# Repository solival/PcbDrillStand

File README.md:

# PCB Drill Press Stand
This is small neat drill press stand designed to use laser printer engines widely sold on ebay/aliexpress.
This project based on http://www.thingiverse.com/thing:144333 by Mark Benson design with next improvements:

- Designed for engine body sized L=35-60mm D=30mm
- Shifted base hole to center drill according new motor diameter
- Added 3x 3mm super light LED holders focused on drill working area
- Added PCB with voltage regulator and connector for standard notebook power unit (which is used for drill and light). This can be easily changed on any power source up to 24v (only connector should be changed in this case)
- Added holes in slider to mount PCB
- Added hole on left side of fixed sliding wedge for balancing spring/rubber.

Apart from that no big changes. I print gears with 40% filament and all other parts with 20% filament. Works fine.

This thing on thingiverse: http://www.thingiverse.com/thing:766712

# Photos
Drill Press Stand assembled

---

Drilling area light

---

Assembled render front

---

Assembled render back:

---

LED Light Schematics

---

LED Light board layout

# Bill of Materials
## Mechanics
- ABS or PLA filament
- Drill chuck
- Threaded rod M5 (about 110mm)
- Threaded rod M8 (about 95mm and 80mm). One is for stand, second is for gear and fixed slider.
- 6x M8 nut, nyloc (better 8x for stand tightening)
- 4x 8mm washer
- 9x M3 18mm bolts
- 10x M3 nuts
- 6x 3mm washers
- 6x 3x12mm screws

## Electronics
- Motor from printer with body diameter 30mm and length between 35-60mm
- Female-Female du-pont wires 10cm (6x)
- 3x LED 3mm White
- 2.54mm 2-wire connector
- Jack plug (diameters must match your notebook power unit connector)
- Notebook power unit
- 2x3 pin header male
- LM7805 (or LM7812) voltage regulator
- 0.1uF and 0.33uF capacitors
- 3x 100 Ohm resistors (or 390 Ohm if LM7812 used)
- Prototype Board or etched PCB

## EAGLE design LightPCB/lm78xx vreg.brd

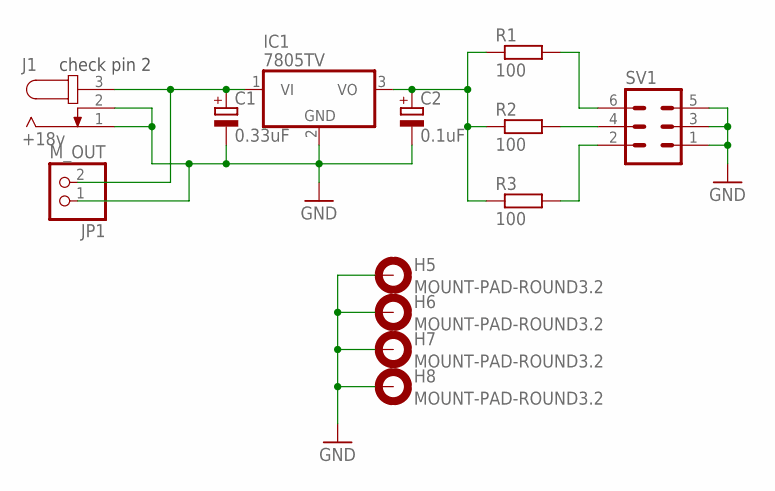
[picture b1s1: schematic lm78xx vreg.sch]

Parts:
C1: 0.33uF; E2,5-7
C2: 0.1uF; E2,5-7
H5, H6, H7, H8: MOUNT-PAD-ROUND3.2; 3,2-PAD
IC1: 7805TV; TO220V
J1: +18v; SPC4078
JP1: M_OUT; 1X02
R1, R2, R3: 100; R0805W
SV1: MA03-2

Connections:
GND: C1.-, C2.-, H5.B3,2, H6.B3,2, H7.B3,2, H8.B3,2, IC1.2 (GND), J1.1, J1.2, JP1.1, SV1.1, SV1.3, SV1.5
unnamed: C1.+, IC1.1 (VI), J1.3, JP1.2
unnamed: C2.+, IC1.3 (VO), R1.1, R2.1, R3.1
unnamed: R2.2, SV1.4
unnamed: R1.2, SV1.6
unnamed: R3.2, SV1.2

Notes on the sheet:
check pin 2

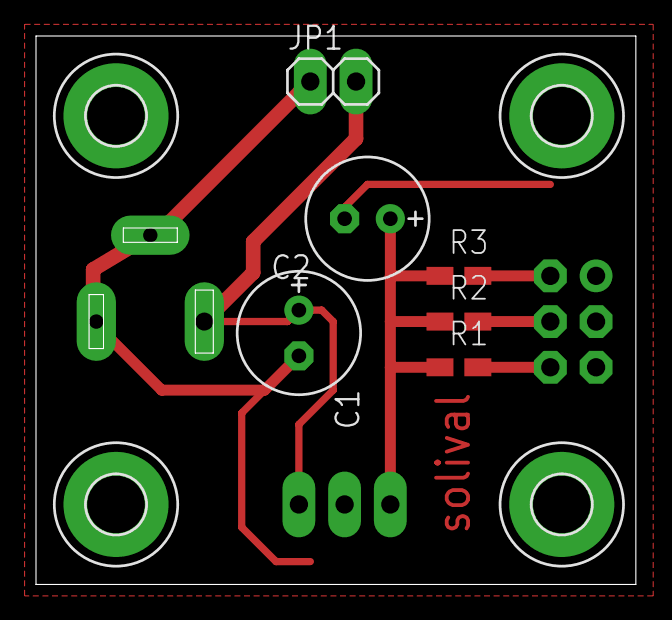
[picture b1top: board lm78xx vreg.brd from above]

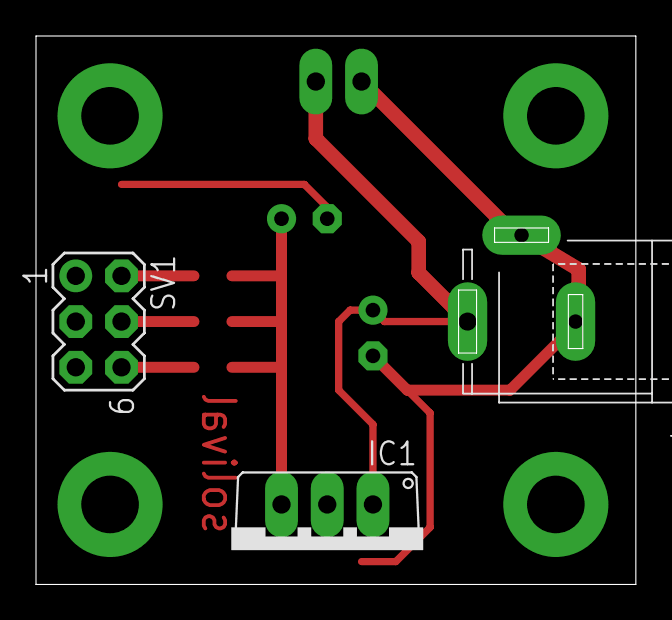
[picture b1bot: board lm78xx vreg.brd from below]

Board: 2 copper layers, 33.3 x 30.5 mm, 13 parts (3 on the bottom side), 6 nets.

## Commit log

2015-02-21 :tada: Added .gitattributes & .gitignore files
2015-02-21 Initial commit
    All files that I have at the moment
2015-03-11 Changed DRC for light PCB
2015-03-28 Bigger distance between traces and ground pane.
2015-04-11 PCB Rill Stand v1
2015-04-11 Documentation imrovements
2015-04-11 Images adopted for web
